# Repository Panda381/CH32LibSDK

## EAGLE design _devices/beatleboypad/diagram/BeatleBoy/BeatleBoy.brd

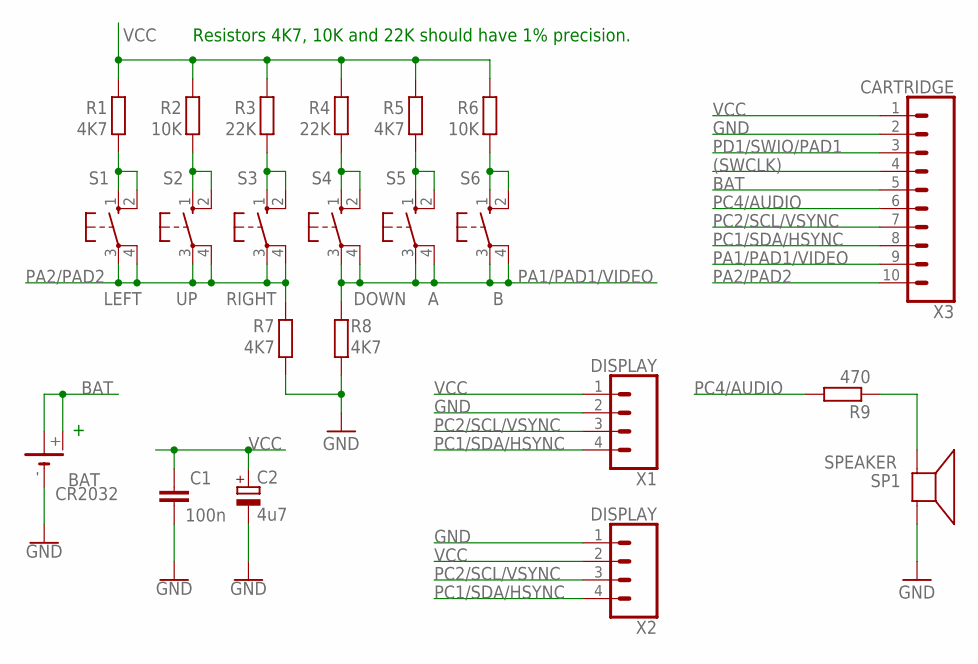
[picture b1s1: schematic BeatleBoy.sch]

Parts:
BAT: CR2032; CR2032H
C1: 100n; C025-024X044
C2: 4u7; E2-4
R1, R5, R7, R8: 4K7; 0204V
R2, R6: 10K; 0204V
R3, R4: 22K; 0204V
R9: 470; 0204V
S1: LEFT; B3F-10XXB
S2: UP; B3F-10XXB
S3: RIGHT; B3F-10XXB
S4: DOWN; B3F-10XXB
S5: A; B3F-10XXB
S6: B; B3F-10XXB
SP1: SPEAKER; AL60P
X1, X2: DISPLAY; 1X04
X3: CARTRIDGE; 1X10_LONGPADS

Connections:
(SWCLK): X3.4
A: R5.2, S5.1 (S), S5.2 (S1)
B: R6.2, S6.1 (S), S6.2 (S1)
BAT: BAT.+, BAT.+@1 (+), X3.5
DOWN: R4.2, S4.1 (S), S4.2 (S1)
GND: BAT.-, C1.2, C2.-, R7.2, R8.2, SP1.2 (-), X1.2, X2.1, X3.2
LEFT: R1.2, S1.1 (S), S1.2 (S1)
unnamed: R9.1, SP1.1 (+)
PA1/PAD1/VIDEO: R8.1, S4.3, S4.4 (P1), S5.3, S5.4 (P1), S6.3, S6.4 (P1), X3.9
PA2/PAD2: R7.1, S1.3, S1.4 (P1), S2.3, S2.4 (P1), S3.3, S3.4 (P1), X3.10
PC1/SDA/HSYNC: X1.4, X2.4, X3.8
PC2/SCL/VSYNC: X1.3, X2.3, X3.7
PC4/AUDIO: R9.2, X3.6
PD1/SWIO/PAD1: X3.3
RIGHT: R3.2, S3.1 (S), S3.2 (S1)
UP: R2.2, S2.1 (S), S2.2 (S1)
VCC: C1.1, C2.+, R1.1, R2.1, R3.1, R4.1, R5.1, R6.1, X1.1, X2.2, X3.1

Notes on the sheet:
Resistors 4K7, 10K and 22K should have 1% precision.

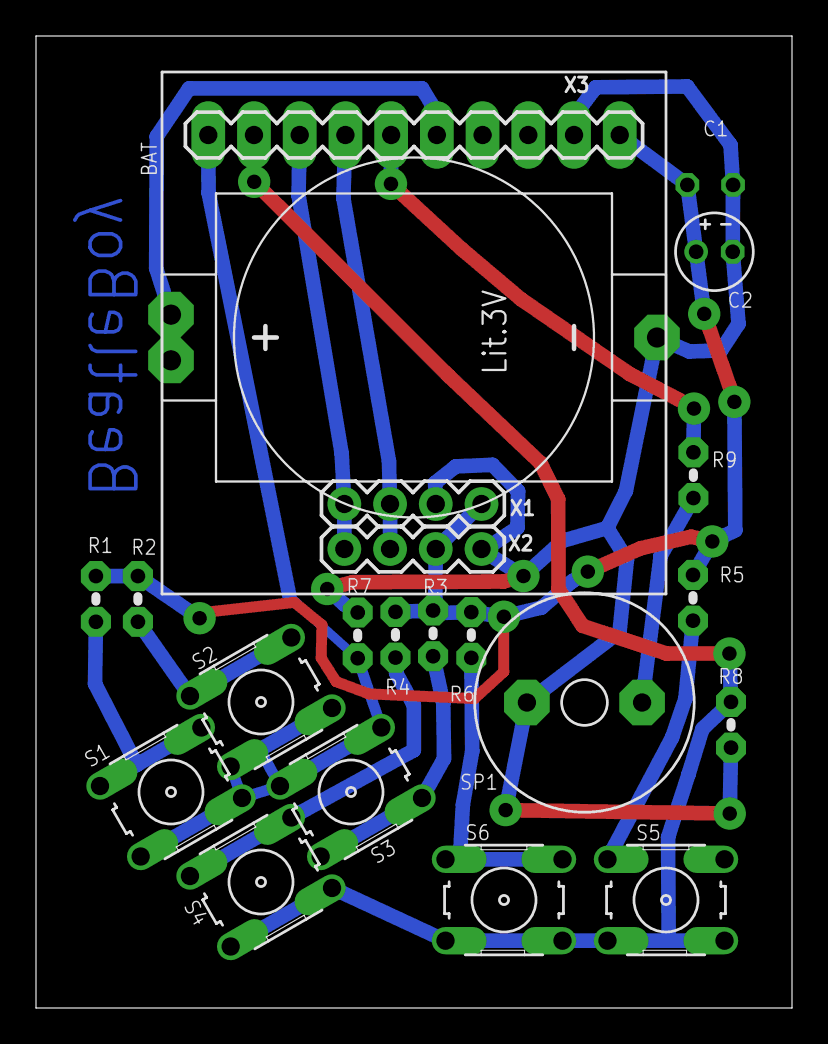
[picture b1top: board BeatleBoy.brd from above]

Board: 2 copper layers, 42.0 x 54.0 mm, 22 parts (1 on the bottom side), 15 nets.

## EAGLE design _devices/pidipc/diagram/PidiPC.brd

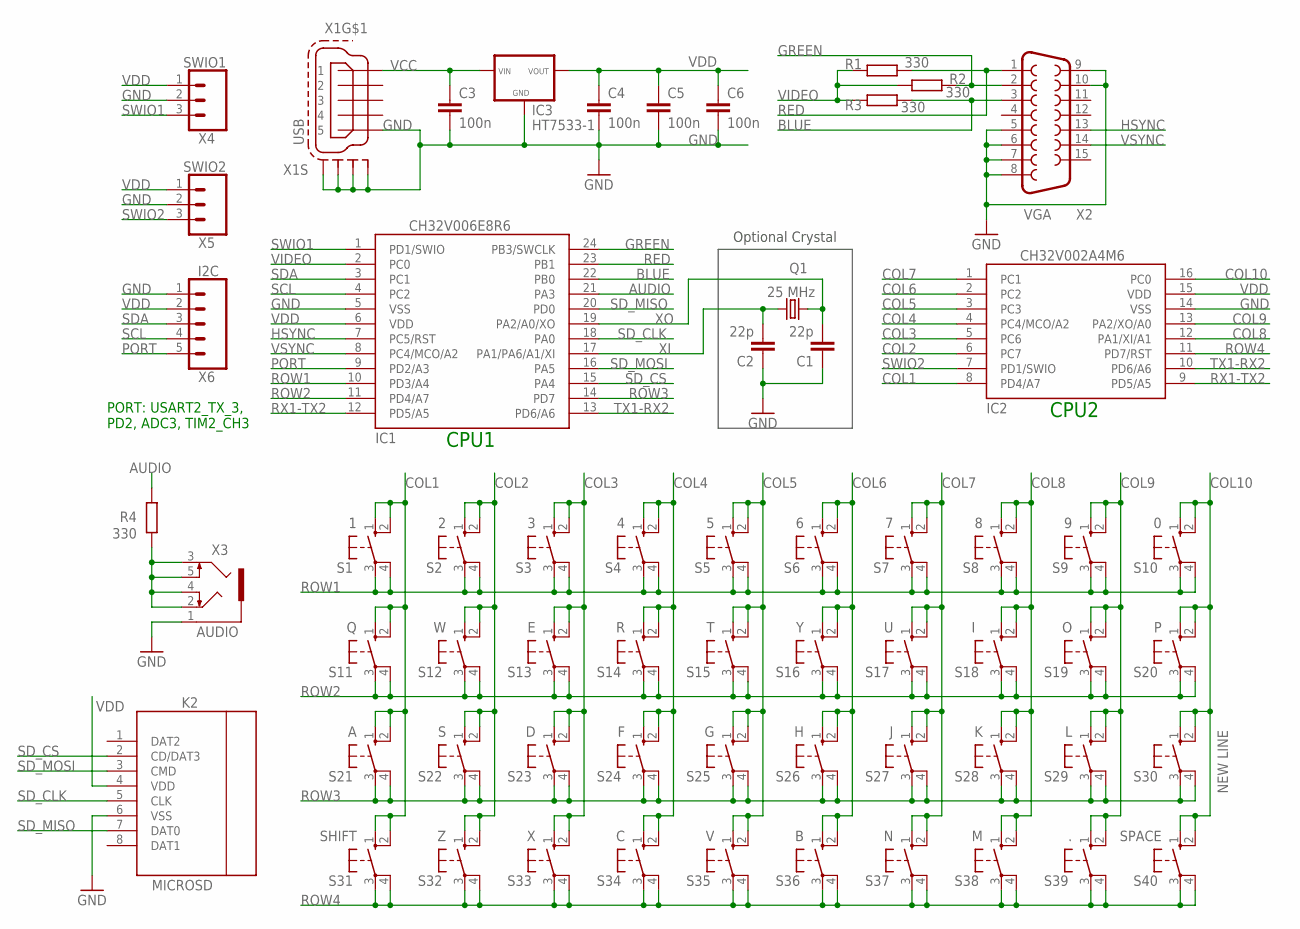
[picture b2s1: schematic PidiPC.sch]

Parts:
C1, C2: 22p; C050-024X044
C3, C4, C5, C6: 100n; C050-024X044
IC1: CH32V006E8R6; QSOP24
IC2: CH32V002A4M6; SOP16
IC3: HT7533-1
K2: MICROSD
Q1: 25 MHz; HC49U-V
R1, R2, R3, R4: 330; 0204/7
S1: 1; B3F-10XX
S2: 2; B3F-10XX
S3: 3; B3F-10XX
S4: 4; B3F-10XX
S5: 5; B3F-10XX
S6: 6; B3F-10XX
S7: 7; B3F-10XX
S8: 8; B3F-10XX
S9: 9; B3F-10XX
S10: 0; B3F-10XX
S11: Q; B3F-10XX
S12: W; B3F-10XX
S13: E; B3F-10XX
S14: R; B3F-10XX
S15: T; B3F-10XX
S16: Y; B3F-10XX
S17: U; B3F-10XX
S18: I; B3F-10XX
S19: O; B3F-10XX
S20: P; B3F-10XX
S21: A; B3F-10XX
S22: S; B3F-10XX
S23: D; B3F-10XX
S24: F; B3F-10XX
S25: G; B3F-10XX
S26: H; B3F-10XX
S27: J; B3F-10XX
S28: K; B3F-10XX
S29: L; B3F-10XX
S30: NEW LINE; B3F-10XX
S31: SHIFT; B3F-10XX
S32: Z; B3F-10XX
S33: X; B3F-10XX
S34: C; B3F-10XX
S35: V; B3F-10XX
S36: B; B3F-10XX
S37: N; B3F-10XX
S38: M; B3F-10XX
S39: .; B3F-10XX
S40: SPACE; B3F-10XX
X1: USB; 32005-201
X2: VGA; HDF15H
X3: AUDIO; 1503_09
X4: SWIO1; 1X03_LONGPADS
X5: SWIO2; 1X03_LONGPADS
X6: I2C; 1X05_LONGPADS

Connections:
AUDIO: IC1.21 (PA3), R4.2
BLUE: IC1.22 (PB0), R3.2, X2.3
COL1: IC2.8 (PD4/A7), S1.1 (S), S1.2 (S1), S11.1 (S), S11.2 (S1), S21.1 (S), S21.2 (S1), S31.1 (S), S31.2 (S1)
COL2: IC2.6 (PC7), S2.1 (S), S2.2 (S1), S12.1 (S), S12.2 (S1), S22.1 (S), S22.2 (S1), S32.1 (S), S32.2 (S1)
COL3: IC2.5 (PC6), S3.1 (S), S3.2 (S1), S13.1 (S), S13.2 (S1), S23.1 (S), S23.2 (S1), S33.1 (S), S33.2 (S1)
COL4: IC2.4 (PC4/MCO/A2), S4.1 (S), S4.2 (S1), S14.1 (S), S14.2 (S1), S24.1 (S), S24.2 (S1), S34.1 (S), S34.2 (S1)
COL5: IC2.3 (PC3), S5.1 (S), S5.2 (S1), S15.1 (S), S15.2 (S1), S25.1 (S), S25.2 (S1), S35.1 (S), S35.2 (S1)
COL6: IC2.2 (PC2), S6.1 (S), S6.2 (S1), S16.1 (S), S16.2 (S1), S26.1 (S), S26.2 (S1), S36.1 (S), S36.2 (S1)
COL7: IC2.1 (PC1), S7.1 (S), S7.2 (S1), S17.1 (S), S17.2 (S1), S27.1 (S), S27.2 (S1), S37.1 (S), S37.2 (S1)
COL8: IC2.12 (PA1/XI/A1), S8.1 (S), S8.2 (S1), S18.1 (S), S18.2 (S1), S28.1 (S), S28.2 (S1), S38.1 (S), S38.2 (S1)
COL9: IC2.13 (PA2/XO/A0), S9.1 (S), S9.2 (S1), S19.1 (S), S19.2 (S1), S29.1 (S), S29.2 (S1), S39.1 (S), S39.2 (S1)
COL10: IC2.16 (PC0), S10.1 (S), S10.2 (S1), S20.1 (S), S20.2 (S1), S30.1 (S), S30.2 (S1), S40.1 (S), S40.2 (S1)
GND: C1.1, C2.1, C3.2, C4.2, C5.2, C6.2, IC1.5 (VSS), IC2.14 (VSS), IC3.GND, K2.6 (VSS), X1.5, X1.M1 (S1), X1.M2 (S2), X1.M3 (S3), X1.M4 (S4), X2.5, X2.6, X2.7, X2.8, X2.9, X2.10, X3.1, X4.2, X5.2, X6.1
GREEN: IC1.24 (PB3/SWCLK), R2.2, X2.2
HSYNC: IC1.7 (PC5/RST), X2.13
unnamed: R4.1, X3.2, X3.3, X3.4, X3.5
PORT: IC1.9 (PD2/A3), X6.5
RED: IC1.23 (PB1), R1.2, X2.1
ROW1: IC1.10 (PD3/A4), S1.3, S1.4 (P1), S2.3, S2.4 (P1), S3.3, S3.4 (P1), S4.3, S4.4 (P1), S5.3, S5.4 (P1), S6.3, S6.4 (P1), S7.3, S7.4 (P1), S8.3, S8.4 (P1), S9.3, S9.4 (P1), S10.3, S10.4 (P1)
ROW2: IC1.11 (PD4/A7), S11.3, S11.4 (P1), S12.3, S12.4 (P1), S13.3, S13.4 (P1), S14.3, S14.4 (P1), S15.3, S15.4 (P1), S16.3, S16.4 (P1), S17.3, S17.4 (P1), S18.3, S18.4 (P1), S19.3, S19.4 (P1), S20.3, S20.4 (P1)
ROW3: IC1.14 (PD7), S21.3, S21.4 (P1), S22.3, S22.4 (P1), S23.3, S23.4 (P1), S24.3, S24.4 (P1), S25.3, S25.4 (P1), S26.3, S26.4 (P1), S27.3, S27.4 (P1), S28.3, S28.4 (P1), S29.3, S29.4 (P1), S30.3, S30.4 (P1)
ROW4: IC2.11 (PD7/RST), S31.3, S31.4 (P1), S32.3, S32.4 (P1), S33.3, S33.4 (P1), S34.3, S34.4 (P1), S35.3, S35.4 (P1), S36.3, S36.4 (P1), S37.3, S37.4 (P1), S38.3, S38.4 (P1), S39.3, S39.4 (P1), S40.3, S40.4 (P1)
RX1-TX2: IC1.12 (PD5/A5), IC2.9 (PD5/A5)
SCL: IC1.4 (PC2), X6.4
SDA: IC1.3 (PC1), X6.3
SD_CLK: IC1.18 (PA0), K2.5 (CLK)
SD_CS: IC1.15 (PA4), K2.2 (CD/DAT3)
SD_MISO: IC1.20 (PD0), K2.7 (DAT0)
SD_MOSI: IC1.16 (PA5), K2.3 (CMD)
SWIO1: IC1.1 (PD1/SWIO), X4.3
SWIO2: IC2.7 (PD1/SWIO), X5.3
TX1-RX2: IC1.13 (PD6/A6), IC2.10 (PD6/A6)
VCC: C3.1, IC3.VIN, X1.1
VDD: C4.1, C5.1, C6.1, IC1.6 (VDD), IC2.15 (VDD), IC3.VOUT, K2.4 (VDD), X4.1, X5.1, X6.2
VIDEO: IC1.2 (PC0), R1.1, R2.1, R3.1
VSYNC: IC1.8 (PC4/MCO/A2), X2.14
XI: C2.2, IC1.17 (PA1/PA6/A1/XI), Q1.2
XO: C1.2, IC1.19 (PA2/A0/XO), Q1.1

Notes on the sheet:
Optional Crystal
CPU1
CPU2
PORT: USART2_TX_3, PD2, ADC3, TIM2_CH3

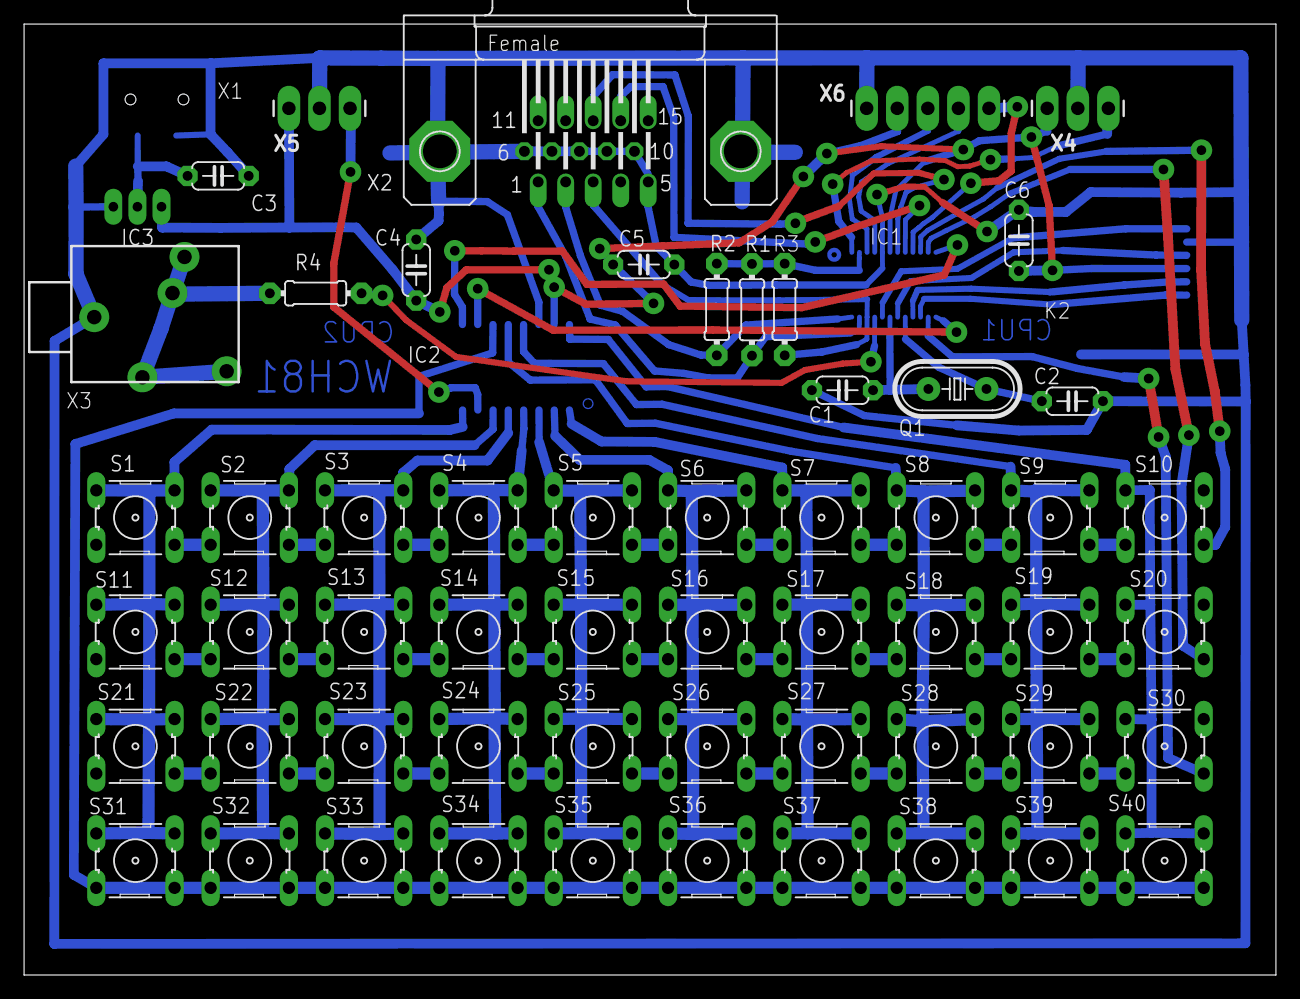
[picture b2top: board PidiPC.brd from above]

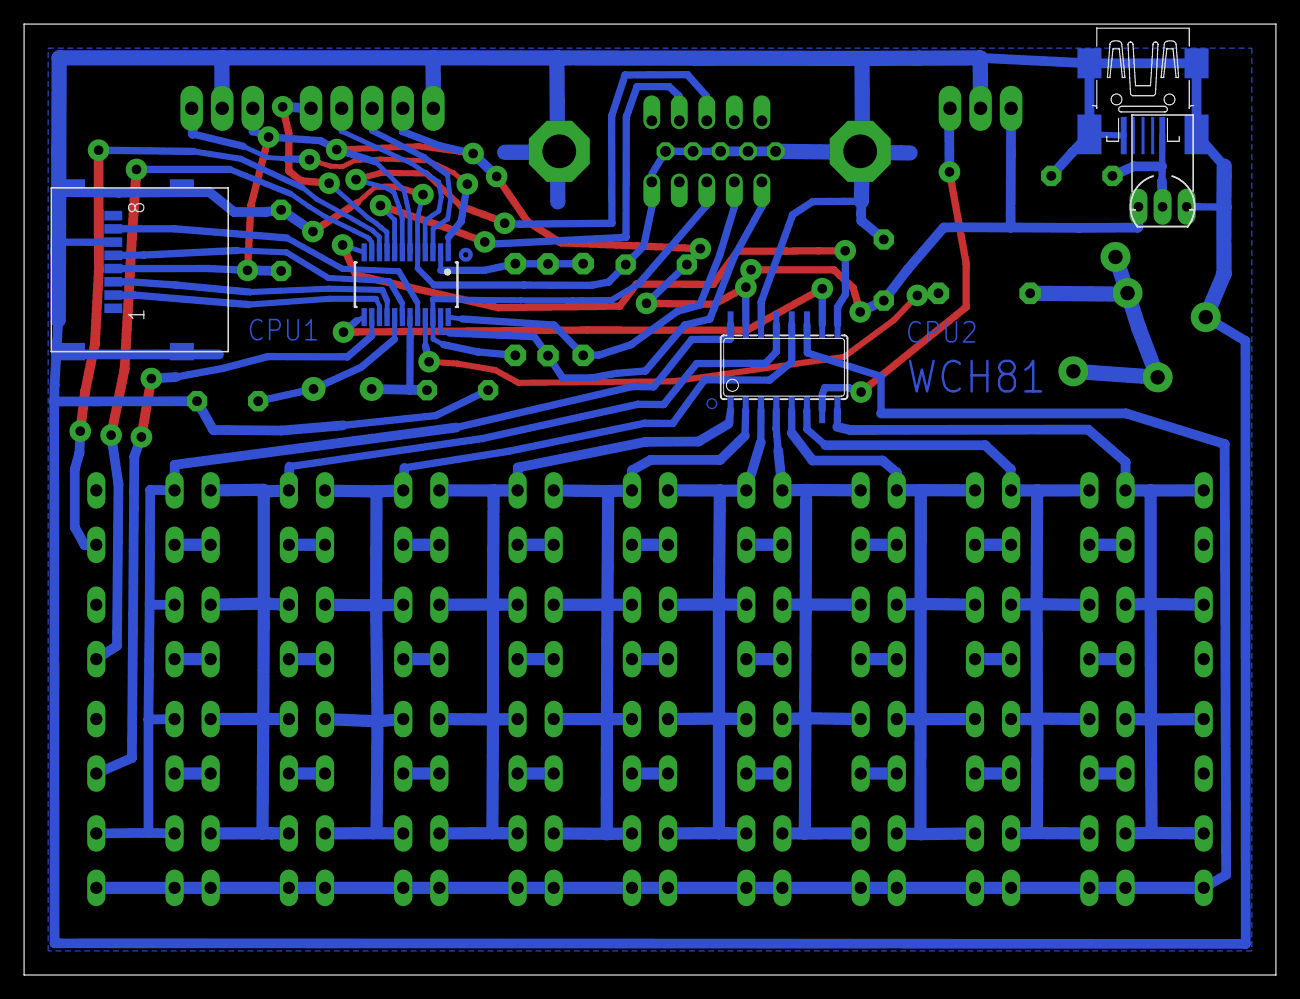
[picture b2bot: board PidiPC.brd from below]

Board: 2 copper layers, 104.0 x 79.0 mm, 61 parts (5 on the bottom side), 38 nets.

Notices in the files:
parts and their libraries:
SparkFun-Connectors: Licensing: Creative Commons ShareAlike 4.0 International - https://creativecommons.org/licenses/by-sa/4.0
Wuerth_Elektronik_eiCan_Communication_Co: Copyright: Würth Elektronik
